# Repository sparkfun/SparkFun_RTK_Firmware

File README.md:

SparkFun RTK Firmware
===========================================================

<table class="table table-hover table-striped table-bordered">
  <tr align="center">
   <td></td>
   <td></td>
   <td></td>
  </tr>
  <tr align="center">
    <td><a href="https://www.sparkfun.com/products/20000"><i>SparkFun RTK Facet L-Band (GPS-20000)</i></a></td>
    <td><a href="https://www.sparkfun.com/products/19029"><i>SparkFun RTK Facet (GPS-19029)</i></a></td>
    <td><a href="https://www.sparkfun.com/products/22429"><i>SparkFun RTK Reference Station (GPS-22429)</i></a></td>
  </tr>
  <tr align="center">
    <td><a href="https://learn.sparkfun.com/tutorials/sparkfun-rtk-facet-l-band-hookup-guide"><i>Hookup Guide</i></a></td>
    <td><a href="https://learn.sparkfun.com/tutorials/sparkfun-rtk-facet-hookup-guide"><i>Hookup Guide</i></a></td>
    <td><a href="https://learn.sparkfun.com/tutorials/sparkfun-rtk-reference-station-hookup-guide"><i>Hookup Guide</i></a></td>
  </tr>
  <tr align="center">
   <td></td>
   <td></td>
   <td></td>
  </tr>
  <tr align="center">
    <td><a href="https://www.sparkfun.com/products/18590"><i>SparkFun RTK Express Plus (GPS-18590)</i></a></td>
    <td><a href="https://www.sparkfun.com/products/18442"><i>SparkFun RTK Express (GPS-18442)</i></a></td>
    <td><a href="https://www.sparkfun.com/products/18443"><i>SparkFun RTK Surveyor (GPS-18443)</i></a></td>
  </tr>
  <tr align="center">
    <td><a href="https://learn.sparkfun.com/tutorials/sparkfun-rtk-express-hookup-guide"><i>Hookup Guide</i></a></td>
    <td><a href="https://learn.sparkfun.com/tutorials/sparkfun-rtk-express-hookup-guide"><i>Hookup Guide</i></a></td>
    <td><a href="https://learn.sparkfun.com/tutorials/sparkfun-rtk-surveyor-hookup-guide"><i>Hookup Guide</i></a></td>
  </tr>
</table>

The [SparkFun RTK Surveyor](https://www.sparkfun.com/products/18443), [SparkFun RTK Express](https://www.sparkfun.com/products/18442), [SparkFun RTK Express Plus](https://www.sparkfun.com/products/18590), [SparkFun RTK Facet](https://www.sparkfun.com/products/19029), [SparkFun RTK Facet L-Band](https://www.sparkfun.com/products/20000) and [SparkFun RTK Reference Station](https://www.sparkfun.com/products/22429) are centimeter-level GNSS receivers. With RTK enabled, these devices can output your location with 14mm horizontal and vertical [*accuracy*](https://docs.sparkfun.com/SparkFun_RTK_Firmware/accuracy_verification/) at up to 20Hz!

This repo houses the [RTK Product Manual](https://docs.sparkfun.com/SparkFun_RTK_Firmware) and the firmware that runs on the SparkFun RTK product line including:

* [SparkFun RTK Facet L-Band](https://www.sparkfun.com/products/20000)
* [SparkFun RTK Facet](https://www.sparkfun.com/products/19029)
* [SparkFun RTK Reference Station](https://www.sparkfun.com/products/22429)
* [SparkFun RTK Express Plus](https://www.sparkfun.com/products/18590)
* [SparkFun RTK Express](https://www.sparkfun.com/products/18442)
* [SparkFun RTK Surveyor](https://www.sparkfun.com/products/18443)

For compiled binaries of the firmware, please see [SparkFun RTK Firmware Binaries](https://github.com/sparkfun/SparkFun_RTK_Firmware_Binaries).

If you're interested in the PCB, enclosure, or overlay on each product please see the hardware repos:

* [SparkFun RTK Facet L-Band Hardware](https://github.com/sparkfun/SparkFun_RTK_Facet)
* [SparkFun RTK Facet Hardware](https://github.com/sparkfun/SparkFun_RTK_Facet)
* [SparkFun RTK Reference Station Hardware](https://github.com/sparkfun/SparkFun_RTK_Reference_Station)
* [SparkFun RTK Express Plus Hardware](https://github.com/sparkfun/SparkFun_RTK_Express_Plus)
* [SparkFun RTK Express Hardware](https://github.com/sparkfun/SparkFun_RTK_Express)
* [SparkFun RTK Surveyor Hardware](https://github.com/sparkfun/SparkFun_RTK_Surveyor)

Thanks:

* Special thanks to [Avinab Malla](https://github.com/avinabmalla) for the creation of [SW Maps](https://play.google.com/store/apps/details?id=np.com.softwel.swmaps&hl=en_US&gl=US) and for pointers on handling the ESP32 read/write tasks.

Documentation
--------------

* **[RTK Product Manual](https://docs.sparkfun.com/SparkFun_RTK_Firmware/)** - A detail guide describing all the various software features of the RTK product line.   Essentially it is a manual for the firmware in this repository.
* **[RTK Facet L-Band Hookup Guide](https://learn.sparkfun.com/tutorials/sparkfun-rtk-facet-l-band-hookup-guide)** - Hookup guide for the SparkFun RTK Facet L-Band.
* **[RTK Facet Hookup Guide](https://learn.sparkfun.com/tutorials/sparkfun-rtk-facet-hookup-guide)** - Hookup guide for the SparkFun RTK Facet.
* **[RTK Reference Station Hookup Guide](https://learn.sparkfun.com/tutorials/sparkfun-rtk-reference-station-hookup-guide)** - Hookup guide for the SparkFun RTK Reference Station.
* **[RTK Express Hookup Guide](https://learn.sparkfun.com/tutorials/sparkfun-rtk-express-hookup-guide)** - Hookup guide for the SparkFun RTK Express and Express Plus.
* **[RTK Surveyor Hookup Guide](https://learn.sparkfun.com/tutorials/sparkfun-rtk-surveyor-hookup-guide)** - Hookup guide for the SparkFun RTK Surveyor.

Repository Contents
-------------------

* **/Firmware** - Source code for SparkFun RTK firmware as well as various feature unit tests
* **/Graphics** - Original bitmap icons for the display
* **/docs** - Markdown pages for the [RTK Product Manual](https://docs.sparkfun.com/SparkFun_RTK_Firmware/)

Repository Branch Structure
---------------------------

This repository has two long-term branches: `main` and `release_candidate`.

With respect to the firmware, `main` is a branch where only changes that are appropriate for all users are applied. Thus, following `main` means updating to normal releases, and perhaps bugfixes to those releases.

In contrast, `release_candidate` is where new code is added as it is developed.

The documentation source code is in docs/ on `main`.  It is built automatically on push and stored in the branch `gh-pages`, from which it is served at the above URL. Documentation changes are pushed directly to main.

Release Process
---------------

A release is made by merging `release_candidate` back to `main`, and then applying a tag to that commit on `main`.

A pre-release is often created using the latest stable release candidate. These binaries will have extra debug statements turned on that will not be present in a formal release, but should not affect behavior of the firmware.

Building from Source
--------------------

For building the firmware, see the [Firmware README](Firmware/readme.md). For compiled binaries of the firmware, please see [SparkFun RTK Firmware Binaries](https://github.com/sparkfun/SparkFun_RTK_Firmware_Binaries).

For the documentation, see [mkdocs.yml](https://github.com/sparkfun/SparkFun_RTK_Firmware/blob/main/mkdocs.yml) and [/workflows/mkdocs.yml](https://github.com/sparkfun/SparkFun_RTK_Firmware/blob/main/.github/workflows/mkdocs.yml).

For building the Uploader_GUI see [SparkFun_RTK_Firmware_Uploader](https://github.com/sparkfun/SparkFun_RTK_Firmware_Uploader). The pyinstaller executables are generated by the [/workflows](https://github.com/sparkfun/SparkFun_RTK_Firmware_Uploader/tree/main/.github/workflows)

For building the u-blox_Update_GUI see [u-blox_Update_GUI](https://github.com/sparkfun/SparkFun_RTK_Firmware_Binaries/tree/main/u-blox_Update_GUI) and the header comments of [RTK_u-blox_Update_GUI.py](https://github.com/sparkfun/SparkFun_RTK_Firmware/blob/main/u-blox_Update_GUI/RTK_u-blox_Update_GUI.py)

License Information
-------------------

This product is _**open source**_!  Please feel free to [contribute](https://docs.sparkfun.com/SparkFun_RTK_Firmware/contribute/) to both the firmware and documentation.

Various bits of the code have different licenses applied. Anything SparkFun wrote is beerware; if you see me (or any other SparkFun employee) at the local, and you've found our code helpful, please buy us a round!

Please use, reuse, and modify these files as you see fit. Please maintain attribution to SparkFun Electronics and release anything derivative under the same license.

Distributed as-is; no warranty is given.

- Your friends at SparkFun.

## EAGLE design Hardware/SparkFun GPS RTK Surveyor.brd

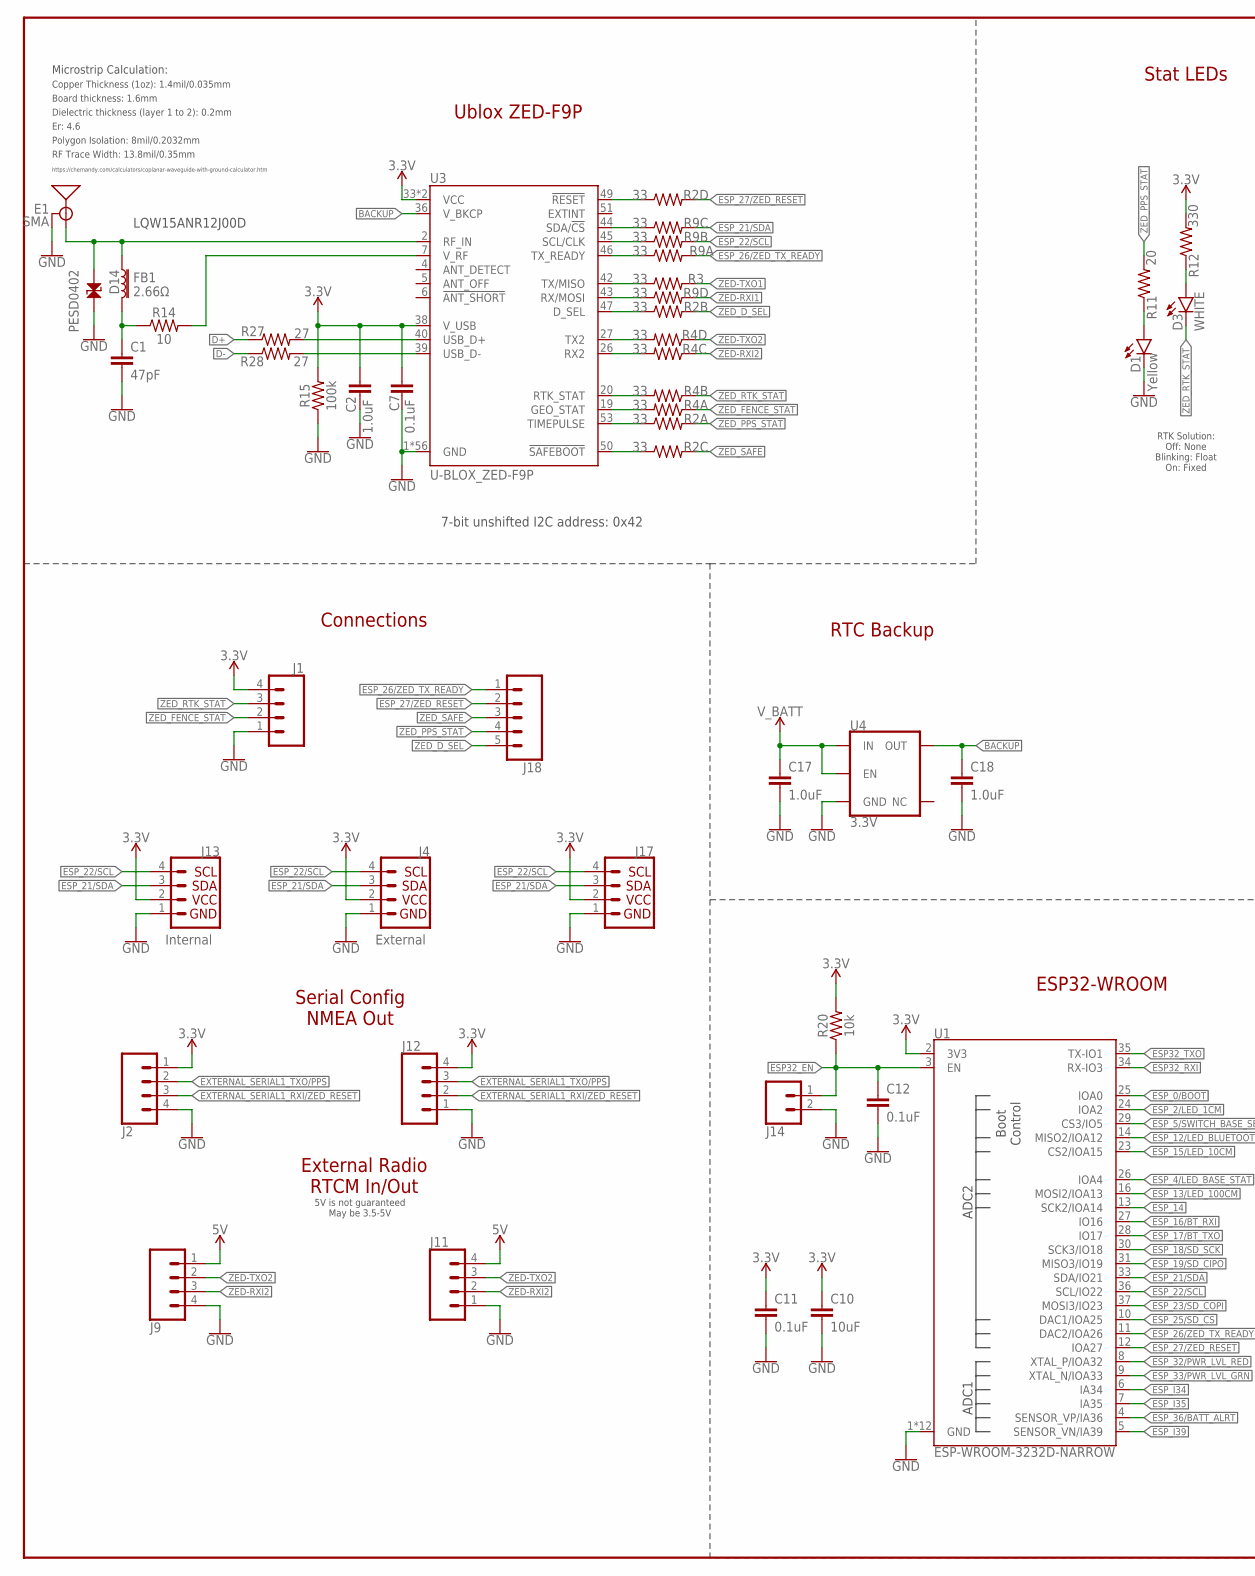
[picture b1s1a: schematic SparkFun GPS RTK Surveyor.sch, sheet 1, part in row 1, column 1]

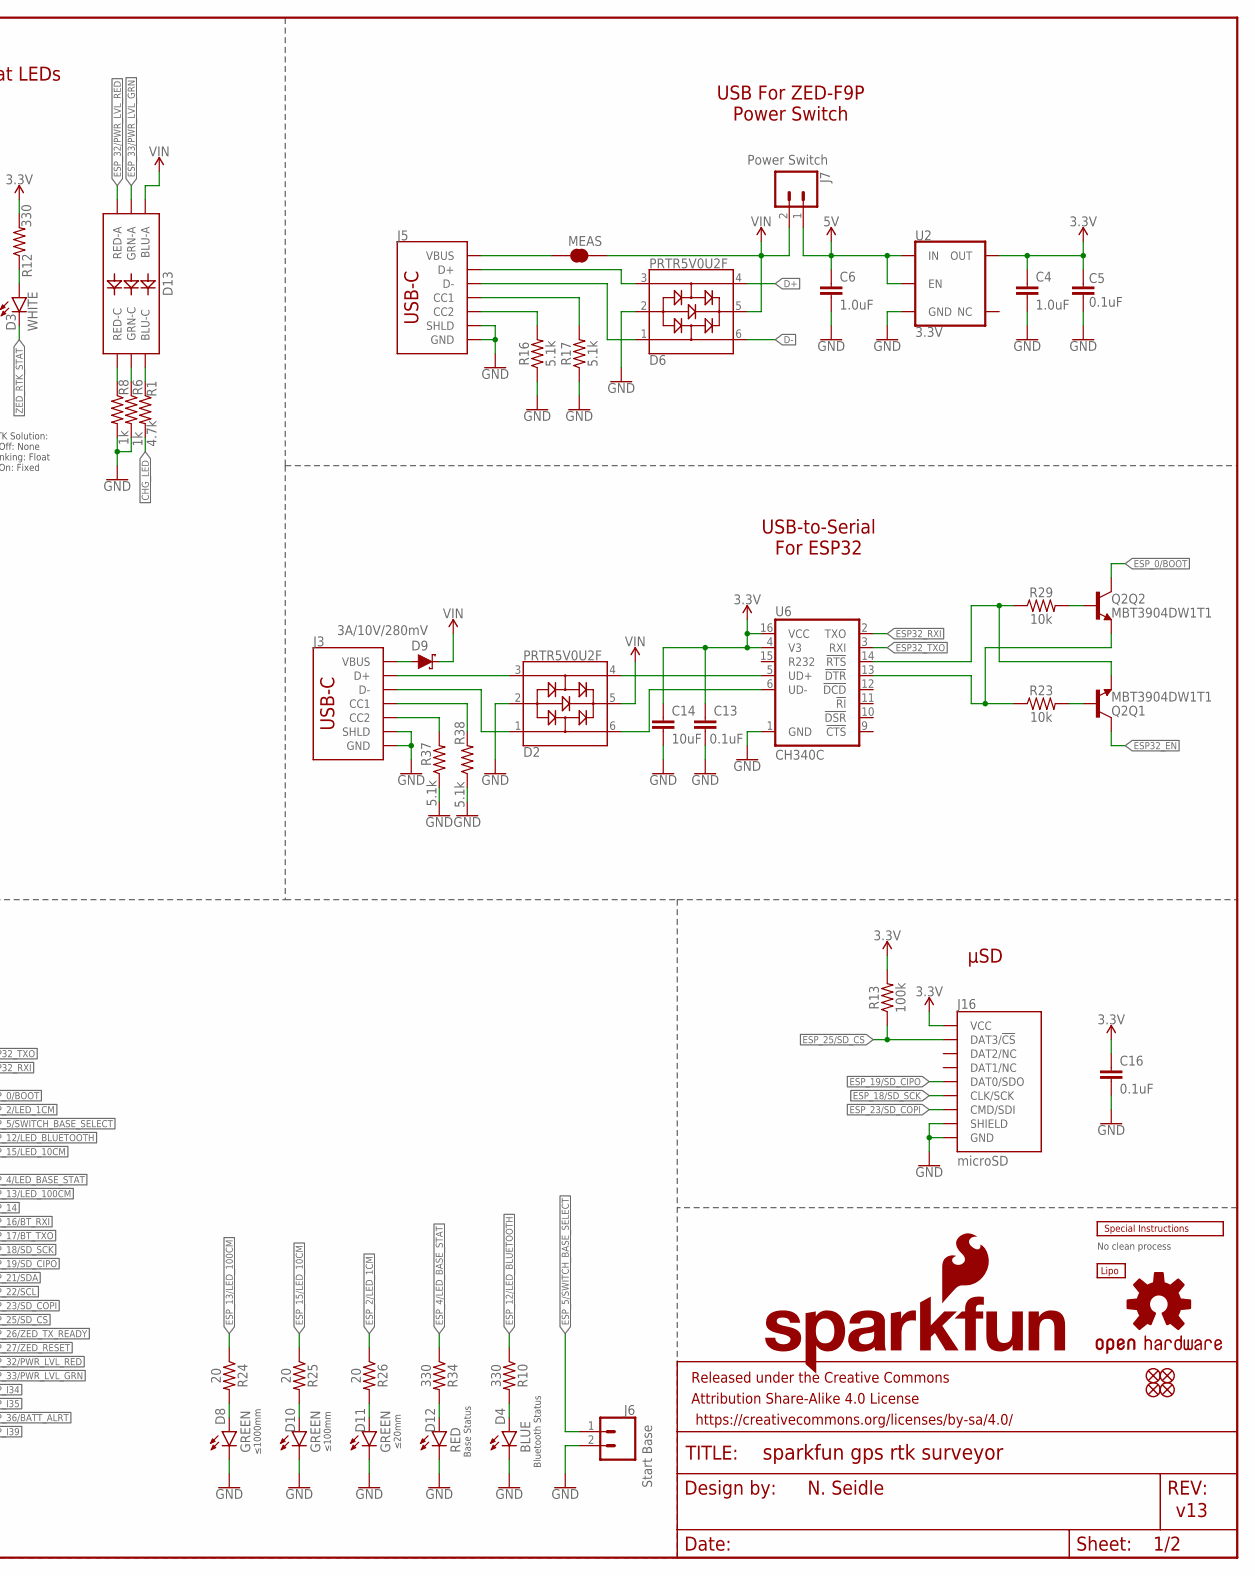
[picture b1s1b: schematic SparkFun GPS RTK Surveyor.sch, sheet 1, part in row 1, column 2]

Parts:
BT1: LIPO-OUTLINE1000; LIPO-1000
C1: 47pF; 0402
C2, C4, C6, C17, C18: 1.0uF; 0603
C5, C7, C11, C12, C13, C16: 0.1uF; 0603
C10, C14: 10uF; 0603
D1: Yellow; LED-0603
D2, D6: PRTR5V0U2F; SOT886
D3: WHITE; LED-0603
D4: BLUE; LED-0603
D8, D10, D11: GREEN; LED-0603
D9: 3A/10V/280mV; SOD-323
D12: RED; LED-0603
D13: LED-RGBBRG; LED-TRICOLOR-5050
D14: PESD0402; 0402
E1: SMA; SMA-EDGE-SMD
FB1: 2.66Ω; 0402-TIGHT
FRAME2: FRAME-LEDGER; CREATIVE_COMMONS
J1, J11, J12: CONN_041X04_NO_SILK_NO_POP; 1X04_NO_SILK
J2, J9: CONN_04JST-SMD-LOCKING; JST-4-SMD-1.25MM-LOCKING
J3, J5: USB Female Type C Connector; USB-C-16P_4LAYER-PADS
J4: External; JST04_1MM_RA
J6: Start Base; JST-2-SMD
J7: Power Switch; JST-2-SMD
J13: Internal; JST04_1MM_RA
J14: CONN_021X02_NO_SILK; 1X02_NO_SILK
J16: microSD; MICRO-SD-SOCKET
J17: Qwiic Right Angle; 1X04_NO_SILK
J18: CONN_05NO_SILK; 1X05_NO_SILK
JP21, JP61, JP71, JP81: FIDUCIALUFIDUCIAL; FIDUCIAL-MICRO
LOGO1: OSHW-LOGOMINI; OSHW-LOGO-MINI
LOGO2: SFE_LOGO_NAME_FLAME.1_INCH; SFE_LOGO_NAME_FLAME_.1
MEAS: JUMPER-COMBO_2_NC_TRACE; COMBO-JUMPER_2_NC_TRACE
Q2: MBT3904DW1T1; SC70-6
R1: 4.7k; 0603
R2, R4, R9: 33; 1206_RA
R3: 33; 0603
R6, R8: 1k; 0603
R10, R12, R34: 330; 0603
R11, R24, R25, R26: 20; 0603
R13, R15: 100k; 0603
R14: 10; 0603
R16, R17, R37, R38: 5.1k; 0603
R20, R23, R29: 10k; 0603
R27, R28: 27; 0603
U1: ESP-WROOM-3232D-NARROW; ESP-WROOM-32D-NARROW
U2, U4: 3.3V; SOT23-5
U3: U-BLOX_ZED-F9P; ZED-F9P
U6: CH340C; SO016
U$2: SPECIAL_INSTRUCTIONS-ORDERING; ORDERING_INSTRUCTIONS

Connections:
3.3V: C2.1, C4.1, C5.2, C7.2, C10.1, C11.1, C13.1, C14.1, C16.1, J1.4, J2.1, J4.2, J12.4, J13.2, J16.VCC, J17.2, R12.2, R13.2, R15.2, R20.2, U1.2 (3V3), U2.5 (OUT), U3.33 (VCC), U3.34 (VCC), U3.38 (V_USB), U6.4 (V3), U6.16 (VCC)
5V: C6.1, J7.1 (2), J9.1, J11.4, U2.1 (IN), U2.3 (EN)
ANT_VCC: C1.1, FB1.2, R14.1
BACKUP: C18.1, U3.36 (V_BKCP), U4.5 (OUT)
CC1: J5.A5 (CC1), R17.2
CC2: J5.B5 (CC2), R16.2
CC3: J3.B5 (CC2), R37.2
CC4: J3.A5 (CC1), R38.2
CHG_LED: R1.2; also elsewhere on the board
D+: D6.4, R27.1
D+1: D2.4, U6.5 (UD+)
D-: D6.6, R28.1
D-1: D2.6, U6.6 (UD-)
ESP32_!DTR: Q2.1 (E), R23.1, U6.13 (!DTR)
ESP32_!RTS: Q2.4 (E), R29.1, U6.14 (!RTS)
ESP32_EN: C12.1, J14.1, Q2.3 (C), R20.1, U1.3 (EN)
ESP32_RXI: U1.34 (RX-IO3), U6.2 (TXO)
ESP32_TXO: U1.35 (TX-IO1), U6.3 (RXI)
ESP_0/BOOT: Q2.6 (C), U1.25 (IOA0)
ESP_2/LED_1CM: R26.1, U1.24 (IOA2)
ESP_4/LED_BASE_STAT: R34.1, U1.26 (IOA4)
ESP_5/SWITCH_BASE_SELECT: J6.1 (2), U1.29 (CS3/IO5)
ESP_12/LED_BLUETOOTH: R10.1, U1.14 (MISO2/IOA12)
ESP_13/LED_100CM: R24.1, U1.16 (MOSI2/IOA13)
ESP_14: U1.13 (SCK2/IOA14)
ESP_15/LED_10CM: R25.1, U1.23 (CS2/IOA15)
ESP_16/BT_RXI: U1.27 (IO16); also elsewhere on the board
ESP_17/BT_TXO: U1.28 (IO17); also elsewhere on the board
ESP_18/SD_SCK: J16.SCLK (CLK/SCK), U1.30 (SCK3/IO18)
ESP_19/SD_CIPO: J16.DO/DAT0 (DAT0/SDO), U1.31 (MISO3/IO19)
ESP_21/SDA: J4.3, J13.3, J17.3, R9.P6 (2), U1.33 (SDA/IO21); also elsewhere on the board
ESP_22/SCL: J4.4, J13.4, J17.4, R9.P7 (2), U1.36 (SCL/IO22); also elsewhere on the board
ESP_23/SD_COPI: J16.DI/CMD (CMD/SDI), U1.37 (MOSI3/IO23)
ESP_25/SD_!CS!: J16.CS/DAT3 (DAT3/!CS!), R13.1, U1.10 (DAC1/IOA25)
ESP_26/ZED_TX_READY: J18.1, R9.P8 (2), U1.11 (DAC2/IOA26)
ESP_26/ZED_TX_READY_LV: R9.P1 (1), U3.46 (TX_READY)
ESP_27/ZED_!RESET!: J18.2, R2.P5 (2), U1.12 (IOA27); also elsewhere on the board
ESP_27/ZED_!RESET!_LV: R2.P4 (1), U3.49 (!RESET!)
ESP_32/PWR_LVL_RED: D13.5 (RED-A), U1.8 (XTAL_P/IOA32)
ESP_33/PWR_LVL_GRN: D13.4 (GRN-A), U1.9 (XTAL_N/IOA33)
ESP_36/BATT_ALRT: U1.4 (SENSOR_VP/IA36); also elsewhere on the board
ESP_D1+: D2.3, J3.A6 (D+), J3.B6 (D+)
ESP_D1-: D2.1, J3.A7 (D-), J3.B7 (D-)
ESP_I34: U1.6 (IA34)
ESP_I35: U1.7 (IA35)
ESP_I39: U1.5 (SENSOR_VN/IA39)
EXTERNAL_SERIAL1_RXI/ZED_!RESET!: J2.3, J12.2; also elsewhere on the board
EXTERNAL_SERIAL1_TXO/PPS: J2.2, J12.3; also elsewhere on the board
FENCE_LV: R4.P8 (2), U3.19 (GEO_STAT)
GND: C1.2, C2.2, C4.2, C5.1, C6.2, C7.1, C10.2, C11.2, C12.2, C13.2, C14.2, C16.2, C17.2, C18.2, D1.C, D2.2, D4.C, D6.2, D8.C, D10.C, D11.C, D12.C, D14.2, E1.GND@0 (GND), E1.GND@1 (GND), J1.1, J2.4, J3.GND, J3.GND2 (GND), J3.SHLD1 (SHLD), J3.SHLD2 (SHLD), J3.SHLD3 (SHLD), J3.SHLD4 (SHLD), J4.1, J5.GND, J5.GND2 (GND), J5.SHLD1 (SHLD), J5.SHLD2 (SHLD), J5.SHLD3 (SHLD), J5.SHLD4 (SHLD), J6.2 (1), J9.4, J11.1, J12.1, J13.1, J14.2, J16.CD1 (SHIELD), J16.GND, J16.GND1 (GND), J16.GND3 (GND), J17.1, R6.2, R8.2, R15.1, R16.1, R17.1, R37.1, R38.1, U1.1 (GND), U1.15 (GND), U1.38 (GND), U1.GND1 (GND), U1.GNDT1 (GND), U1.GNDT2 (GND), U1.GNDT3 (GND), U1.GNDT4 (GND), U1.GNDT5 (GND), U1.GNDT6 (GND), U1.GNDT7 (GND), U1.GNDT8 (GND), U2.2 (GND), U3.1 (GND), U3.3 (GND), U3.12 (GND), U3.14 (GND), U3.32 (GND), U3.37 (GND), U3.41 (GND), U3.48 (GND), U3.55 (GND), U3.56 (GND), U3.57 (GND), U3.58 (GND), U3.59 (GND), U3.60 (GND), U3.61 (GND), U3.62 (GND), U3.63 (GND), U3.64 (GND), U3.65 (GND), U3.66 (GND), U3.67 (GND), U3.68 (GND), U3.69 (GND), U3.70 (GND), U3.71 (GND), U3.72 (GND), U3.73 (GND), U3.74 (GND), U3.75 (GND), U3.76 (GND), U3.77 (GND), U3.78 (GND), U3.79 (GND), U3.80 (GND), U3.81 (GND), U3.82 (GND), U3.83 (GND), U3.84 (GND), U3.85 (GND), U3.86 (GND), U3.87 (GND), U3.88 (GND), U3.89 (GND), U3.90 (GND), U3.91 (GND), U3.92 (GND), U3.93 (GND), U3.94 (GND), U3.95 (GND), U3.96 (GND), U3.97 (GND), U3.98 (GND), U3.99 (GND), U3.100 (GND), U3.101 (GND), U3.102 (GND), U4.2 (GND), U6.1 (GND); also elsewhere on the board
GPS_ANT1: D14.1, E1.SIG (SIGNAL), FB1.1, U3.2 (RF_IN)
unnamed: D3.A, R12.1
unnamed: D1.A, R11.1
unnamed: D4.A, R10.2
unnamed: J5.VBUS1 (VBUS), J5.VBUS2 (VBUS), MEAS.1, MEAS.3 (1)
unnamed: D13.1 (BLU-C), R1.1
unnamed: D13.3 (GRN-C), R6.1
unnamed: D13.2 (RED-C), R8.1
unnamed: R27.2, U3.40 (USB_D+)
unnamed: R28.2, U3.39 (USB_D-)
unnamed: R14.2, U3.7 (V_RF)
unnamed: Q2.5 (B), R23.2
unnamed: Q2.2 (B), R29.2
unnamed: D8.A, R24.2
unnamed: D10.A, R25.2
unnamed: D11.A, R26.2
unnamed: D12.A, R34.2
unnamed: D9.A, J3.VBUS1 (VBUS), J3.VBUS2 (VBUS)
PPS: R2.P1 (1), U3.53 (TIMEPULSE)
RTK_LV: R4.P7 (2), U3.20 (RTK_STAT)
RX2_LV: R4.P6 (2), U3.26 (RX2)
RXLV: R9.P4 (1), U3.43 (RX/MOSI)
SCL_LV: R9.P2 (1), U3.45 (SCL/CLK)
SDA_LV: R9.P3 (1), U3.44 (SDA/!CS!)
TX2_LV: R4.P5 (2), U3.27 (TX2)
TXLV: R3.1, U3.42 (TX/MISO)
UNP_D+: D6.3, J5.A6 (D+), J5.B6 (D+)
UNP_D-: D6.1, J5.A7 (D-), J5.B7 (D-)
VIN: D2.5, D6.5, D9.C, D13.6 (BLU-A), J7.2 (1), MEAS.2, MEAS.4 (2); also elsewhere on the board
V_BATT: C17.1, U4.1 (IN), U4.3 (EN); also elsewhere on the board
ZED-RXI1: R9.P5 (2); also elsewhere on the board
ZED-RXI2: J9.3, J11.2, R4.P3 (1); also elsewhere on the board
ZED-TXO1: R3.2; also elsewhere on the board
ZED-TXO2: J9.2, J11.3, R4.P4 (1); also elsewhere on the board
ZED_!SAFE!: J18.3, R2.P6 (2)
ZED_!SAFE!_LV: R2.P3 (1), U3.50 (!SAFEBOOT!)
ZED_D_SEL: J18.5, R2.P7 (2)
ZED_D_SEL_LV: R2.P2 (1), U3.47 (D_SEL)
ZED_FENCE_STAT: J1.2, R4.P1 (1)
ZED_PPS_STAT: J18.4, R2.P8 (2), R11.2; also elsewhere on the board
ZED_RTK_STAT: D3.C, J1.3, R4.P2 (1)

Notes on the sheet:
v13
7-bit unshifted I2C address: 0x42
Ublox ZED-F9P
RTC Backup
Stat LEDs
LQW15ANR12J00D
Board thickness: 1.6mm
Er: 4.6
Copper Thickness (1oz): 1.4mil/0.035mm
RF Trace Width: 13.8mil/0.35mm
Polygon Isolation: 8mil/0.2032mm
No clean process
Dielectric thickness (layer 1 to 2): 0.2mm
https://chemandy.com/calculators/coplanar-waveguide-with-ground-calculator.htm
Microstrip Calculation:
Connections
External Radio RTCM In/Out
Serial Config NMEA Out
Base Status
≤1000mm
≤100mm
≤20mm
ESP32-WROOM
USB-to-Serial For ESP32
RTK Solution: Off: None Blinking: Float On: Fixed
Bluetooth Status
μSD
5V is not guaranteed May be 3.5-5V
USB For ZED-F9P Power Switch
N. Seidle

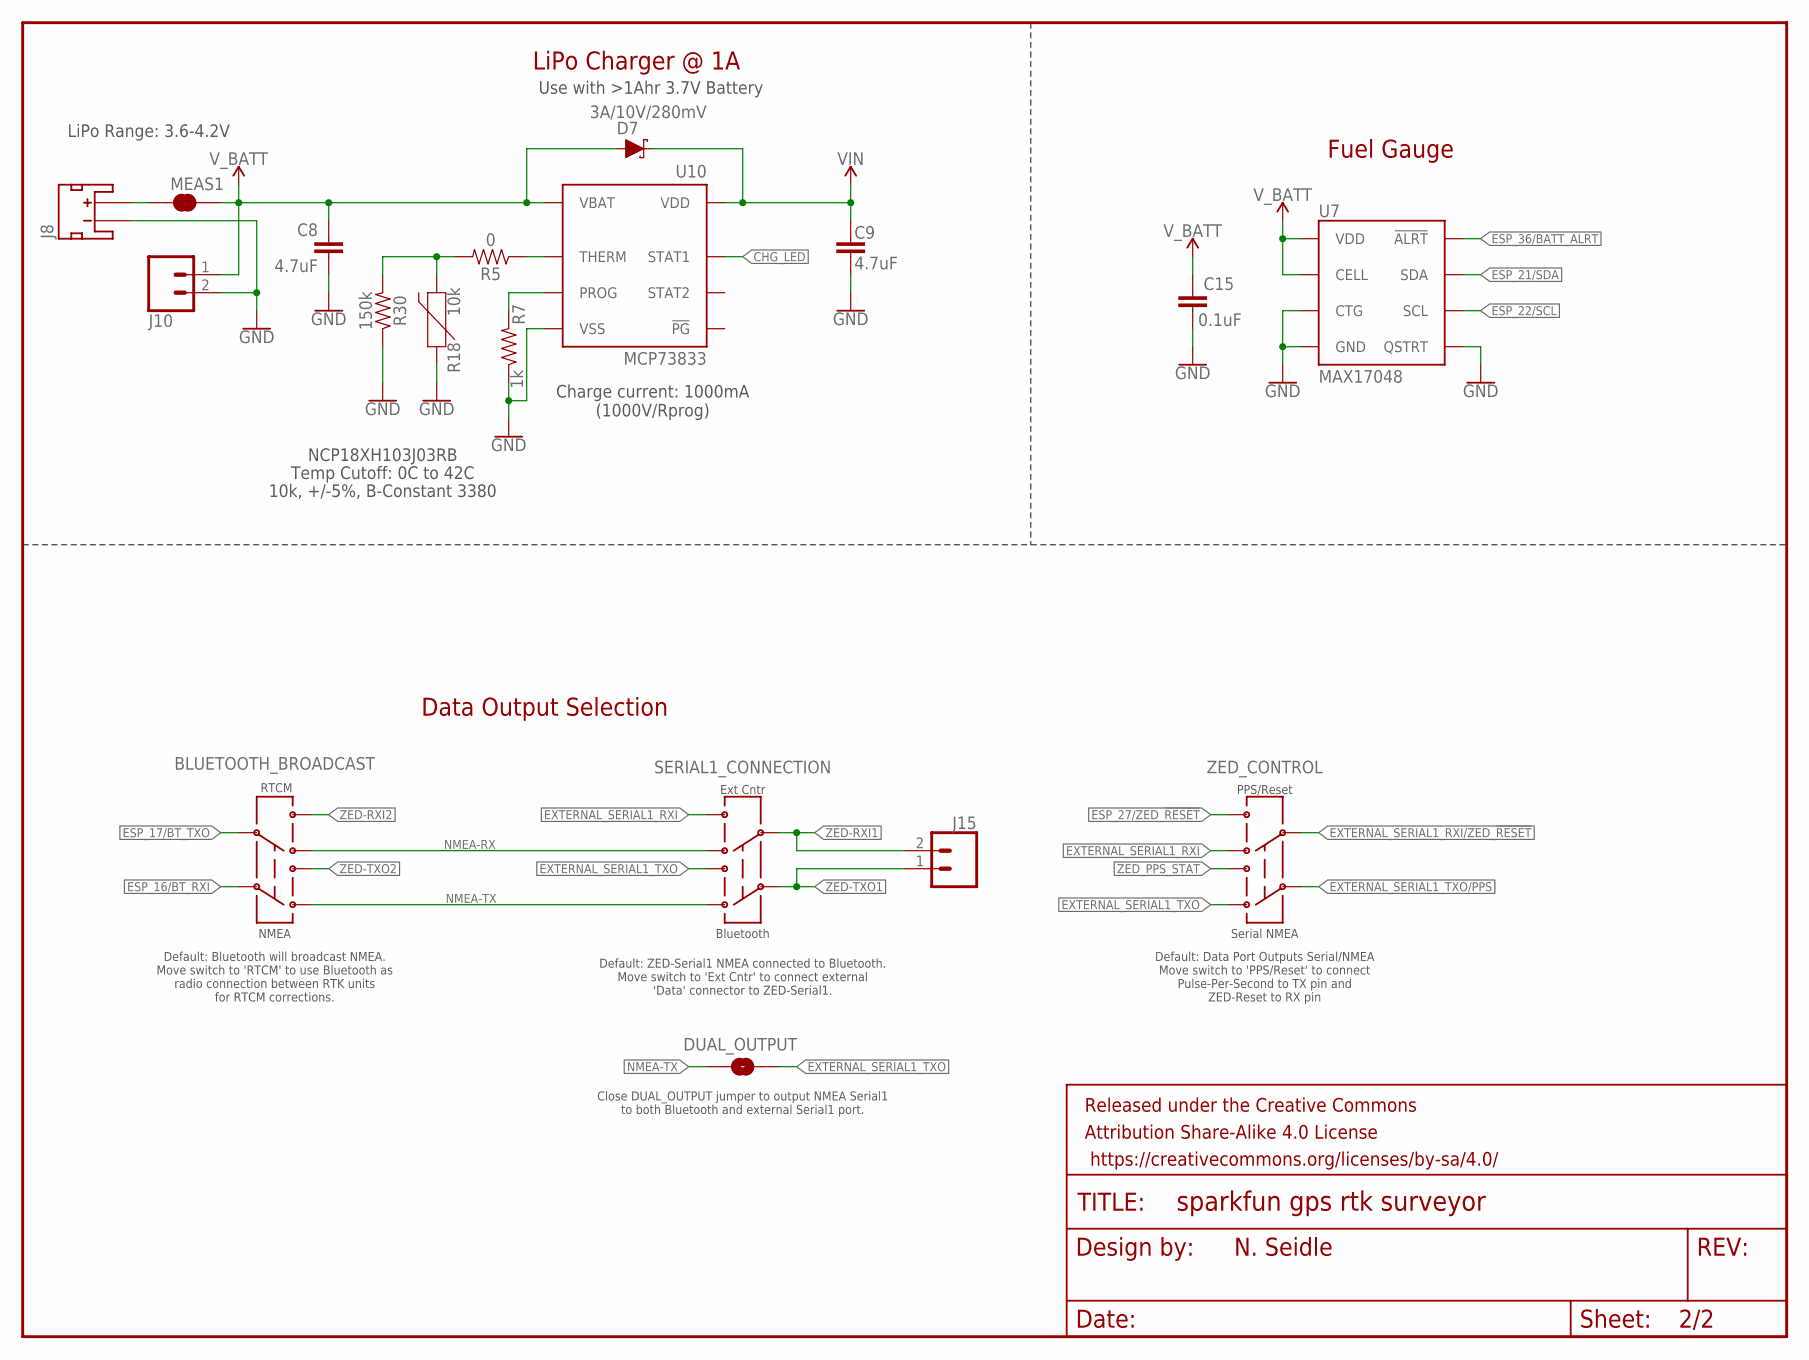
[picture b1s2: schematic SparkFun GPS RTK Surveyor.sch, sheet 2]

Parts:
BLUETOOTH_BROADCAST: SWITCH-DPDT-SMD-AYZ0202; SWITCH_DPDT_SMD_AYZ0202
C8, C9: 4.7uF; 0603
C15: 0.1uF; 0603
D7: 3A/10V/280mV; SOD-323
DUAL_OUTPUT: JUMPER-SMT_2_NO_SILK; SMT-JUMPER_2_NO_SILK
FRAME1: FRAME-LETTERNO_PACKAGE; DUMMY
J8: JST_2MM_MALE; JST-2-SMD
J10, J15: CONN_021X02_NO_SILK; 1X02_NO_SILK
MEAS1: JUMPER-COMBO_2_NC_TRACE; COMBO-JUMPER_2_NC_TRACE
R5: 0; 0603
R7: 1k; 0603
R18: 10k; 0603
R30: 150k; 0603
SERIAL1_CONNECTION: SWITCH-DPDT-SMD-AYZ0202; SWITCH_DPDT_SMD_AYZ0202
U7: MAX17048; DFN-8
U10: MCP73833; DFN-10
ZED_CONTROL: SWITCH-DPDT-SMD-AYZ0202; SWITCH_DPDT_SMD_AYZ0202

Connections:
CHG_LED: U10.3 (STAT1); also elsewhere on the board
CHG_THERM1: R5.2, R18.2, R30.2
ESP_16/BT_RXI: BLUETOOTH_BROADCAST.2; also elsewhere on the board
ESP_17/BT_TXO: BLUETOOTH_BROADCAST.5; also elsewhere on the board
ESP_21/SDA: U7.8 (SDA); also elsewhere on the board
ESP_22/SCL: U7.7 (SCL); also elsewhere on the board
ESP_27/ZED_!RESET!: ZED_CONTROL.4; also elsewhere on the board
ESP_36/BATT_ALRT: U7.5 (!ALRT); also elsewhere on the board
EXTERNAL_SERIAL1_RXI: SERIAL1_CONNECTION.4, ZED_CONTROL.6
EXTERNAL_SERIAL1_RXI/ZED_!RESET!: ZED_CONTROL.5; also elsewhere on the board
EXTERNAL_SERIAL1_TXO: DUAL_OUTPUT.2, SERIAL1_CONNECTION.1, ZED_CONTROL.3
EXTERNAL_SERIAL1_TXO/PPS: ZED_CONTROL.2; also elsewhere on the board
GND: C8.2, C9.2, C15.2, J8.1 (-), J10.2, R7.1, R18.1, R30.1, U7.1 (CTG), U7.4 (GND), U7.6 (QSTRT), U7.9 (GND), U10.5 (VSS), U10.11 (VSS); also elsewhere on the board
LIPO_RAW: J8.2 (+), MEAS1.1, MEAS1.3 (1)
unnamed: R5.1, U10.8 (THERM)
NMEA-RX: BLUETOOTH_BROADCAST.6, SERIAL1_CONNECTION.6
NMEA-TX: BLUETOOTH_BROADCAST.3, DUAL_OUTPUT.1, SERIAL1_CONNECTION.3
PROG1: R7.2, U10.6 (PROG)
VIN: C9.1, D7.C, U10.1 (VDD), U10.2 (VDD); also elsewhere on the board
V_BATT: C8.1, C15.1, D7.A, J10.1, MEAS1.2, MEAS1.4 (2), U7.2 (CELL), U7.3 (VDD), U10.9 (VBAT), U10.10 (VBAT); also elsewhere on the board
ZED-RXI1: J15.2, SERIAL1_CONNECTION.5; also elsewhere on the board
ZED-RXI2: BLUETOOTH_BROADCAST.4; also elsewhere on the board
ZED-TXO1: J15.1, SERIAL1_CONNECTION.2; also elsewhere on the board
ZED-TXO2: BLUETOOTH_BROADCAST.1; also elsewhere on the board
ZED_PPS_STAT: ZED_CONTROL.1; also elsewhere on the board

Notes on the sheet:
LiPo Range: 3.6-4.2V
Charge current: 1000mA (1000V/Rprog)
Use with >1Ahr 3.7V Battery
LiPo Charger @ 1A
NCP18XH103J03RB
10k, +/-5%, B-Constant 3380
Temp Cutoff: 0C to 42C
Fuel Gauge
Default: Bluetooth will broadcast NMEA. Move switch to 'RTCM' to use Bluetooth as radio connection between RTK units for RTCM corrections.
Default: ZED-Serial1 NMEA connected to Bluetooth. Move switch to 'Ext Cntr' to connect external 'Data' connector to ZED-Serial1.
Close DUAL_OUTPUT jumper to output NMEA Serial1 to both Bluetooth and external Serial1 port.
Data Output Selection
RTCM
NMEA
Ext Cntr
Bluetooth
N. Seidle
Default: Data Port Outputs Serial/NMEA Move switch to 'PPS/Reset' to connect Pulse-Per-Second to TX pin and ZED-Reset to RX pin
PPS/Reset
Serial NMEA

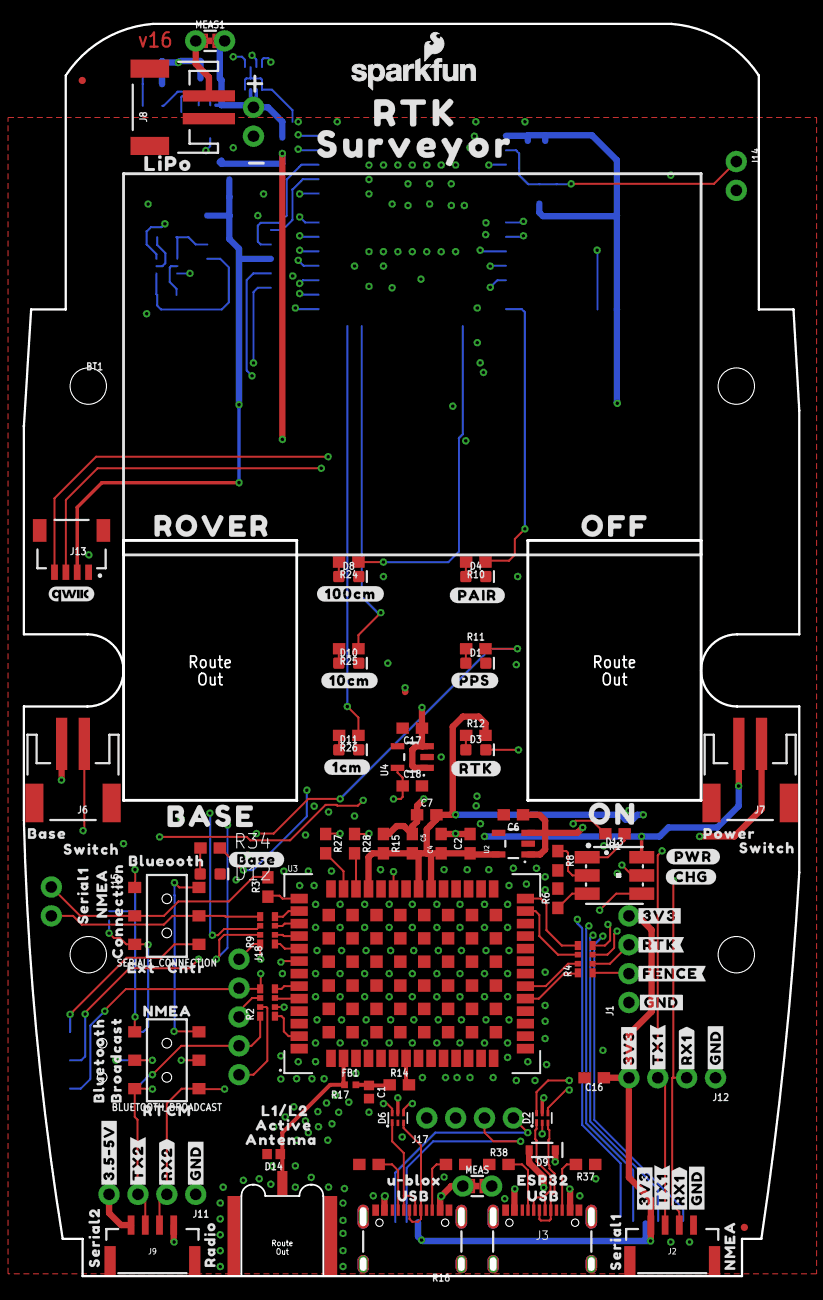
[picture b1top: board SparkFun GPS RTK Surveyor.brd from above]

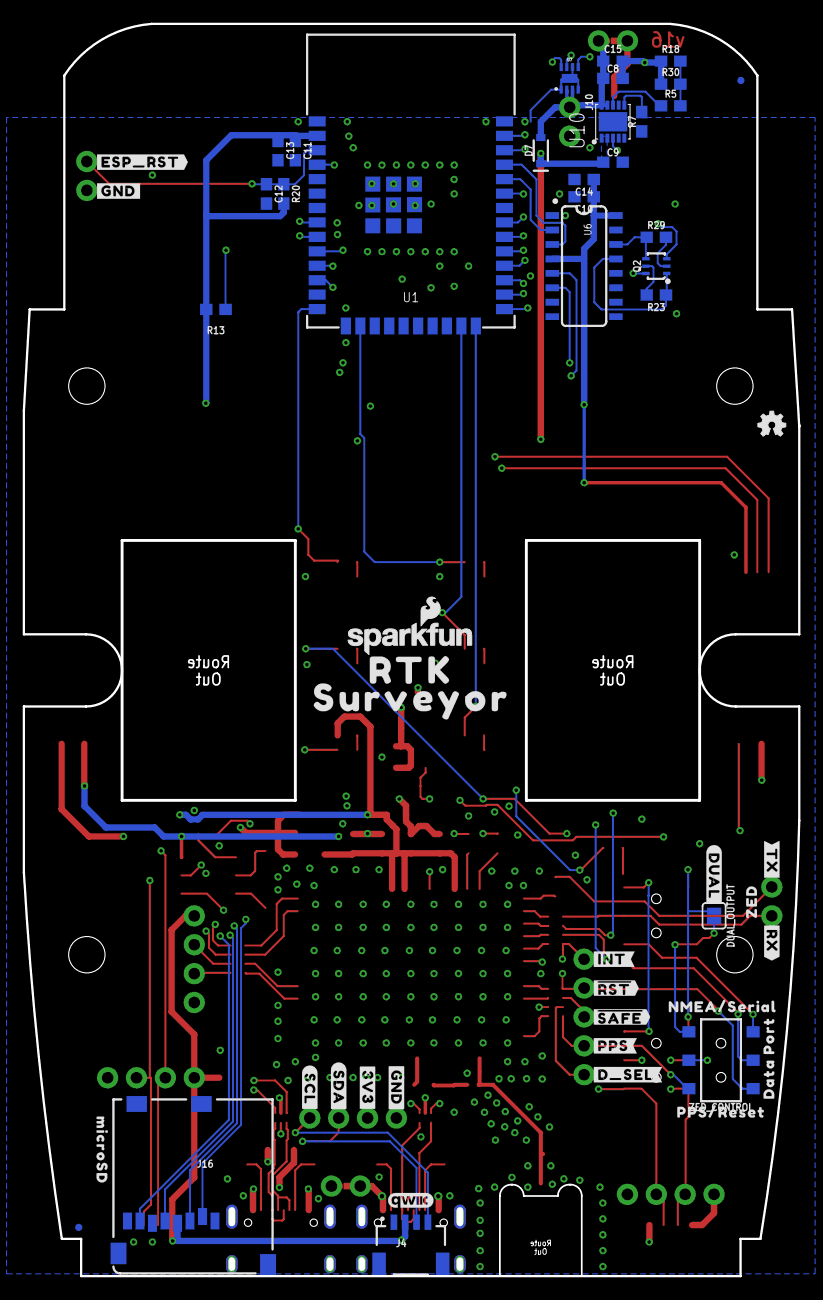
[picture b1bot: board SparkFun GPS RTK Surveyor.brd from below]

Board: 4 copper layers, 68.2 x 110.1 mm, 197 parts (54 on the bottom side), 95 nets.

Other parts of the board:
LOGO3: SFE_LOGO_NAME_FLAME.1_INCH; SFE_LOGO_NAME_FLAME_.1
U$1, U$38, U$48, U$82: #GND#0
U$3, U$34: ROCKER_SWITCH
U$4: #BASE#0
U$5, U$37, U$47: #3V3#0
U$6: ANTENNA0
U$7, U$74: RTK0
U$8: #CHG#0
U$9, U$71: _SURVEYOR3
U$10: #RTK#1
U$11: #PPS#0
U$12: #RTK#0
U$13, U$15, U$21, U$69, U$75, U$76, U$77, U$78: LIGHT_PIPE_3MM
U$14: #RX#2
U$16: ZED0
U$17: ##SAFE##5
U$18: ACTIVE0
U$19: L1#L21
U$20: #PAIR#0
U$22: BASE2
U$23: #3#5#5V#0
U$24: #PPS#1
U$25: #PWR#2
U$26: 1553DBK-ENCLOSURE
U$27: LIPO0
U$28: ##RST##4
U$29, U$63: SERIAL10
U$30, U$93: QWIIC_4MM
U$31: OFF1
U$32: #FENCE#3
U$33: #INT#0
U$35: U#BLOX0
U$36, U$66: USB1
U$39: #RX2#2
U$40: #TX2#1
U$41: BLUETOOTH2
U$42: ON0
U$43: SERIAL20
U$44: ROVER3
U$45, U$68: #RX1#2
U$46, U$65: #TX1#1
U$49, U$52: NMEA1
U$50: RADIO0
U$51: BROADCAST3
U$53: RTCM0
U$54: BASE0
U$55, U$57: SWITCH1
U$56: POWER0
U$58: BLUEOOTH3
U$59: CNTR1
U$60: #ESP_RST#0
U$61: EXT0
U$62: NMEA2
U$64: CONNECTION1
U$67: ESP320
U$70: #GND#2
U$72: #TX#1
U$73: #DUAL#0
U$79: #1CM#0
U$80: #10CM#1
U$81: #100CM#2
U$83: MICROSD0
U$84: #GND#1
U$85: #3V3#2
U$86: #SCL#1
U$87: #SDA#0
U$88: #D_SEL#0
U$89: DATA2
U$90: PORT3
U$91: PPS#RESET0
U$92: NMEA#SERIAL1

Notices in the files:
parts and their libraries:
SparkFun-Resistors: Licensing: Creative Commons ShareAlike 4.0 International - https://creativecommons.org/licenses/by-sa/4.0
SparkFun-Aesthetics: Released under the Creative Commons Attribution Share-Alike 4.0 License
SparkFun-Aesthetics: https://creativecommons.org/licenses/by-sa/4.0
